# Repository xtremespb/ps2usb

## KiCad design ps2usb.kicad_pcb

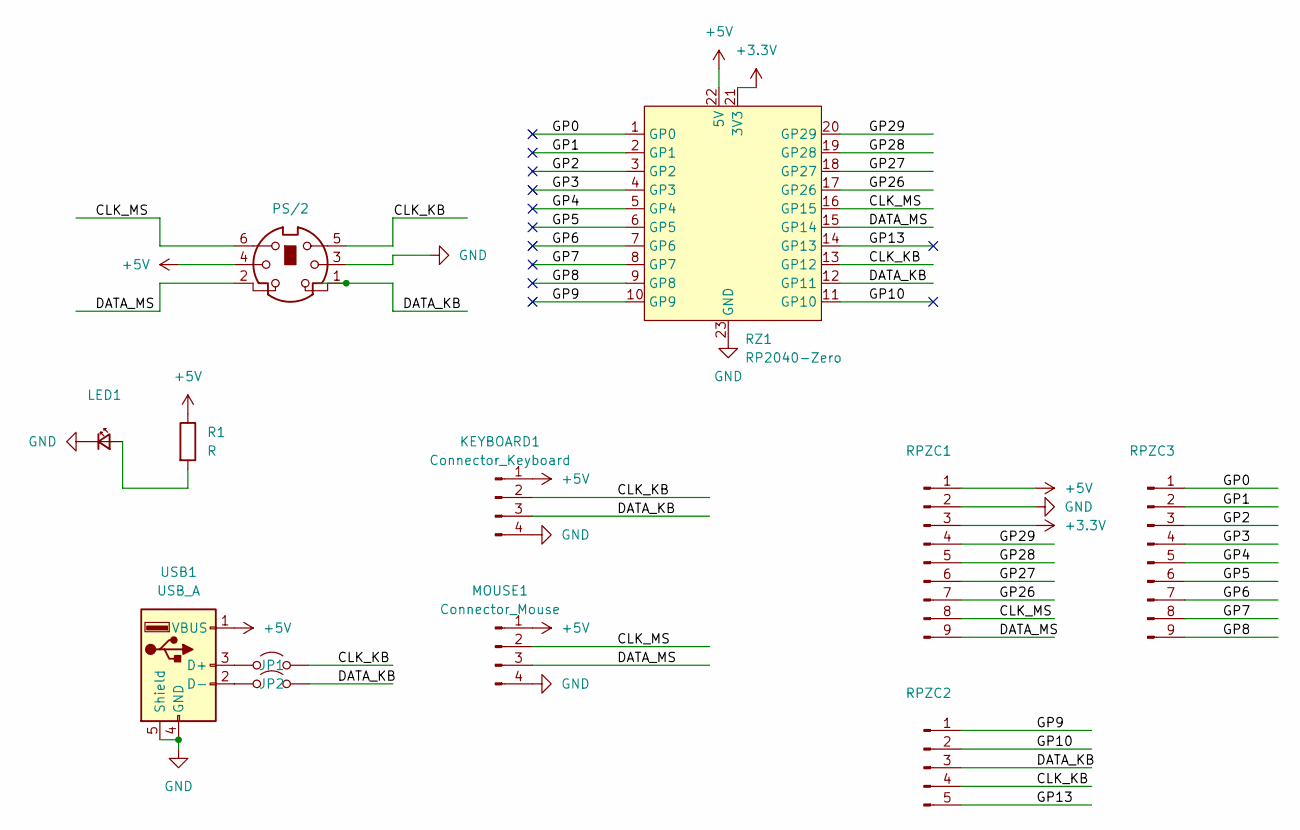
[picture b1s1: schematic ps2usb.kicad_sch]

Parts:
JP1, JP2: Jumper_2_Open; SolderJumper-2_P1.3mm_Open_RoundedPad1.0x1.5mm
KEYBOARD1: Connector_Keyboard; PinHeader_1x04_P2.54mm_Vertical
LED1: LED_Small; R_0805_Medved
MOUSE1: Connector_Mouse; PinHeader_1x04_P2.54mm_Vertical
PS/2: Connector_Mini-DIN_Female_6Pin_2rows
R1: R; R_0805_Medved
RPZC1, RPZC3: Conn_01x09_Pin; PinHeader_1x09_P2.54mm_Vertical
RPZC2: Conn_01x05_Pin; PinHeader_1x05_P2.54mm_Vertical
RZ1: RP2040-Zero; rp2040-zero-tht
USB1: USB_A; USB_A_CONNFLY_DS1095-WNR0

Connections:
+3.3V: RPZC1.3, RZ1.21 (3V3)
+5V: KEYBOARD1.1, MOUSE1.1, PS/2.4, R1.1, RPZC1.1, RZ1.22 (5V), USB1.1 (VBUS)
/CLK_KB: JP1.2 (B), KEYBOARD1.2, PS/2.5, RPZC2.4, RZ1.13 (GP12)
/CLK_MS: MOUSE1.2, PS/2.6, RPZC1.8, RZ1.16 (GP15)
/DATA_KB: JP2.2 (B), KEYBOARD1.3, PS/2.1, RPZC2.3, RZ1.12 (GP11)
/DATA_MS: MOUSE1.3, PS/2.2, RPZC1.9, RZ1.15 (GP14)
/GP0: RPZC3.1, RZ1.1 (GP0)
/GP1: RPZC3.2, RZ1.2 (GP1)
/GP2: RPZC3.3, RZ1.3 (GP2)
/GP3: RPZC3.4, RZ1.4 (GP3)
/GP4: RPZC3.5, RZ1.5 (GP4)
/GP5: RPZC3.6, RZ1.6 (GP5)
/GP6: RPZC3.7, RZ1.7 (GP6)
/GP7: RPZC3.8, RZ1.8 (GP7)
/GP8: RPZC3.9, RZ1.9 (GP8)
/GP9: RPZC2.1, RZ1.10 (GP9)
/GP10: RPZC2.2, RZ1.11 (GP10)
/GP13: RPZC2.5, RZ1.14 (GP13)
/GP26: RPZC1.7, RZ1.17 (GP26)
/GP27: RPZC1.6, RZ1.18 (GP27)
/GP28: RPZC1.5, RZ1.19 (GP28)
/GP29: RPZC1.4, RZ1.20 (GP29)
GND: KEYBOARD1.4, LED1.1 (K), MOUSE1.4, PS/2.3, RPZC1.2, RZ1.23 (GND), USB1.4 (GND), USB1.5 (Shield)
unnamed: JP1.1 (A), USB1.3 (D+)
unnamed: JP2.1 (A), USB1.2 (D-)
unnamed: LED1.2 (A), R1.2

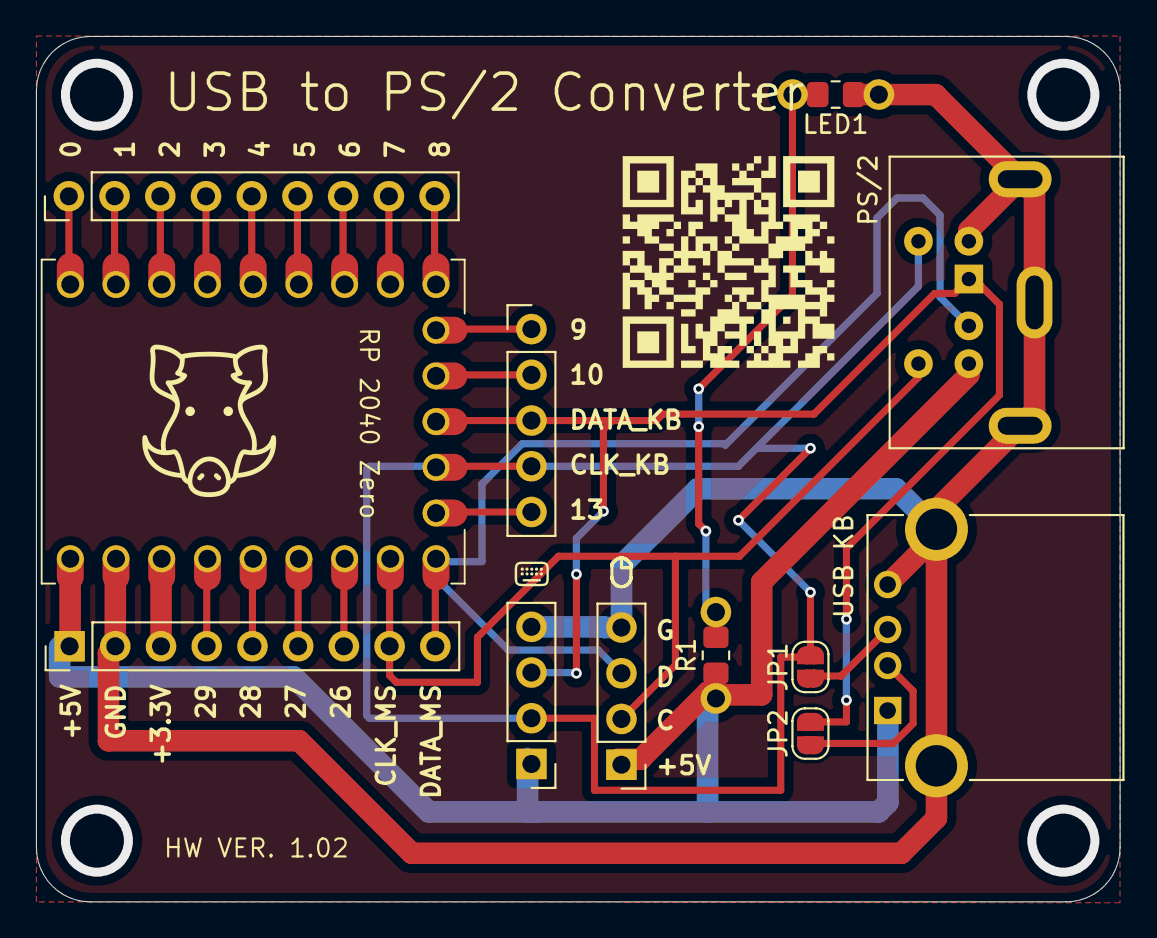
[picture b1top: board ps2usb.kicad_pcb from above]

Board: 2 copper layers, 60.2 x 48.1 mm, 12 parts (0 on the bottom side), 26 nets.

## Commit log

2024-08-06 HW 1.01 Gerber Files
2024-08-19 HW 1.2
2024-08-19 HW 1.2 updates
